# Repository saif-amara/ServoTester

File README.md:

# ServoTester 🎛️

A compact **PWM servo motor tester** PCB designed in **KiCad 9**, built around the classic **NE555 timer IC** in astable mode. Turn the potentiometer — the servo follows.

---

## ⚙️ How It Works

The **NE555P** is configured in **astable (free-running) mode**, generating a continuous PWM signal. A potentiometer (**RV2**) adjusts the RC time constants, which changes the duty cycle of the output pulse — directly controlling the servo motor's angular position.

| PWM Pulse Width | Servo Position |
|---|---|
| ~1 ms | 0° (full left) |
| ~1.5 ms | 90° (center) |
| ~2 ms | 180° (full right) |

---

## 🔌 Connectors

| Connector | Function |
|---|---|
| **J1** (2-pin) | Power input (5V DC) |
| **J2** (3-pin) | Servo output — Signal / VCC / GND |

---

## 🧩 Bill of Materials (BOM)

| Ref | Component | Value / Part |
|---|---|---|
| U1 | Timer IC | NE555P |
| D1 | LED | Power indicator |
| D2 | Diode | 1N4148 |
| RV2 | Potentiometer | 100kΩ |
| R1 | Resistor | 1kΩ |
| R3 | Resistor | 56kΩ |
| R4 | Resistor | (see schematic) |
| C1 | Capacitor | (see schematic) |
| J1 | Connector | Conn_01x02 |
| J2 | Connector | Conn_01x03 |

---

## 📐 PCB Specifications

- **Layers:** 2 (F.Cu / B.Cu)
- **Software:** KiCad 9.0
- **Board label:** `servo motor tester`
- **Designer initials:** SEA

---

## 🚀 How to Open

1. Install **[KiCad 9](https://www.kicad.org/download/)**
2. Clone this repository:
   ```bash
   git clone https://github.com/saif-amara/ServoTester.git
   ```
3. Open `ServoTester.kicad_pro` in KiCad
4. Open schematic: `ServoTester.kicad_sch`
5. Open PCB layout: `ServoTester.kicad_pcb`

---

## 📁 Project Structure

```
ServoTester/
├── ServoTester.kicad_pro     # KiCad project file
├── ServoTester.kicad_sch     # Schematic
├── ServoTester.kicad_pcb     # PCB layout
├── .gitignore
└── README.md
```

---

## 👤 Author

**Saif Eddine Amara**  
Embedded Systems Engineering Student — ISSAT Sousse, Tunisia  
Teaching Assistant, Robotics Lab

---

## 📄 License

This project is open-source under the [MIT License](LICENSE).# ServoTester
KiCad 9 PCB design for servo tester circuit

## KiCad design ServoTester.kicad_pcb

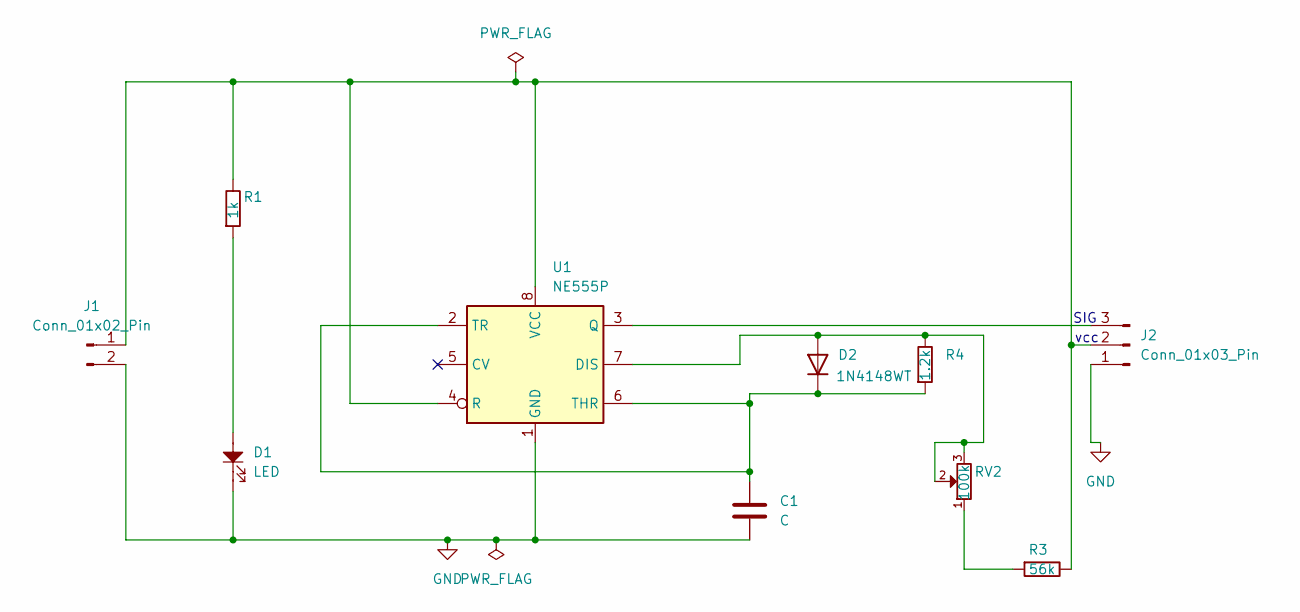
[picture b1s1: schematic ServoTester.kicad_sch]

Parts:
C1: C; C_0504_1310Metric_Pad0.83x1.28mm_HandSolder
D1: LED; LED_D5.0mm
D2: 1N4148WT; D_SOD-523
J1: Conn_01x02_Pin; PhoenixContact_GMSTBA_2,5_2-G-7,62_1x02_P7.62mm_Horizontal
J2: Conn_01x03_Pin; PhoenixContact_GMSTBA_2,5_3-G-7,62_1x03_P7.62mm_Horizontal
R1: 1k; R_Axial_DIN0207_L6.3mm_D2.5mm_P10.16mm_Horizontal
R3: 56k; R_Axial_DIN0207_L6.3mm_D2.5mm_P10.16mm_Horizontal
R4: 1.2k; R_Axial_DIN0207_L6.3mm_D2.5mm_P10.16mm_Horizontal
RV2: 100k; Potentiometer_Alps_RK163_Single_Horizontal
U1: NE555P; DIP-8_W7.62mm

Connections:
GND: C1.2, D1.1, J1.2, J2.1, U1.1 (GND)
unnamed: D1.2, R1.1
unnamed: D2.2 (A), R4.2, RV2.2, RV2.3, U1.7 (DIS)
unnamed: C1.1, D2.1 (K), R4.1, U1.2 (TR), U1.6 (THR)
unnamed: J1.1, J2.2, R1.2, R3.2, U1.4 (R), U1.8 (VCC)
unnamed: J2.3, U1.3 (Q)
unnamed: R3.1, RV2.1

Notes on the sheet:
SIG
vcc

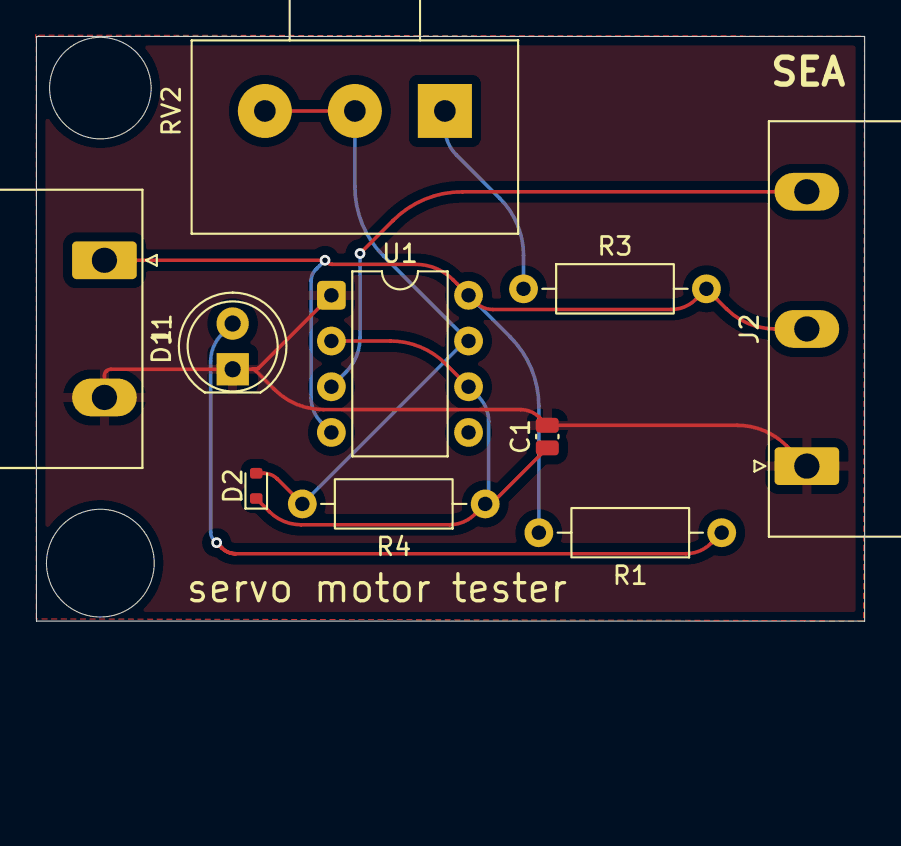
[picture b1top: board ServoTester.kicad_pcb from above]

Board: 2 copper layers, 46.0 x 32.5 mm, 10 parts (0 on the bottom side), 7 nets.

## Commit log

2026-05-19 Initial commit: ServoTester KiCad 9 PCB design
2026-05-19 Update .gitignore for KiCad files
    Add entries to ignore KiCad auto-generated files and backups.
2026-05-19 Remove cached files and update .gitignore
2026-05-19 Revise README for ServoTester project
    Updated README to enhance project description and structure.
2026-05-19 Add professional README with 3D preview
